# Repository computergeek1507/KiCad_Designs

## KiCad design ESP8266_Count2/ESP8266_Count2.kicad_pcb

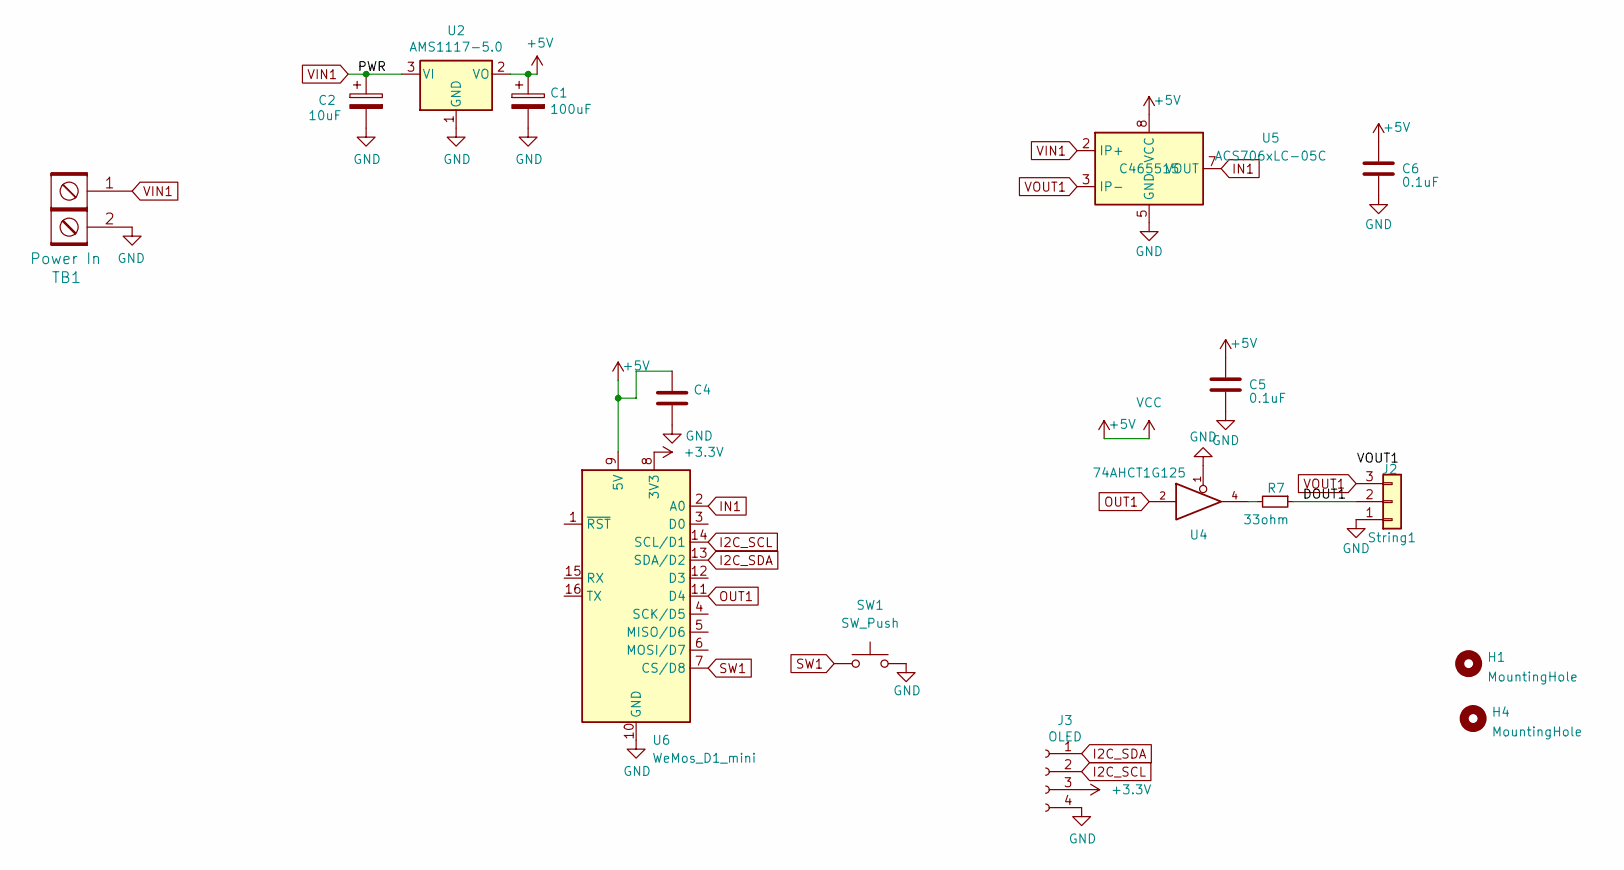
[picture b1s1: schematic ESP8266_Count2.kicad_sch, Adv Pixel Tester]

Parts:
C1: 100uF; C_1206_3216Metric_Pad1.33x1.80mm_HandSolder; LCSC C15008
C2: 10uF; C_0805_2012Metric_Pad1.18x1.45mm_HandSolder; MPN GRM21BR61E106KA73L; Digi-Key_PN 490-5523-1-ND
C4: 0.1uF; C_0603_1608Metric_Pad1.08x0.95mm_HandSolder
C5, C6: 0.1uF; C_0603_1608Metric_Pad1.08x0.95mm_HandSolder; LCSC C14663
H1, H4: MountingHole; MountingHole_2.7mm_M2.5
J2: String1; PhoenixContact_MCV_1,5_3-G-3.81_1x03_P3.81mm_Vertical; MPN 1843619/OSTTJ0311530; Digi-Key_PN 277-5737-ND/ED10555-ND
J3: OLED; OLED-SSD1306-128X64-I2C-THT_2HOLE; MPN PPTC041LFBN-RC; Digi-Key_PN S7002-ND
R7: 33ohm; R_0603_1608Metric_Pad0.98x0.95mm_HandSolder; MPN RC0603JR-0733RL; LCSC_PN C23140
SW1: SW_Push; SW_Push_1P1T_NO_6x6mm_H9.5mm; LCSC C2834918
TB1: Power In; PhoenixContact_MCV_1,5_2-G-3.81_1x02_P3.81mm_Vertical; MPN 4DB-P108-02; Digi-Key_PN A98472-ND
U2: AMS1117-5.0; SOT-223-3_TabPin2; MPN LM1117MPX-50NOPB; LCSC_PN C6187
U4: 74AHCT1G125; TSOP-5_1.65x3.05mm_P0.95mm; MPN 74AHCT1G125W5-7; Digi-Key_PN 74AHCT1G125W5-7DICT-ND
U5: ACS706xLC-05C; SOIC-8_3.9x4.9mm_P1.27mm; LCSC C465515
U6: WeMos_D1_mini; WEMOS_D1_mini_light

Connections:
+3.3V: J3.3, U6.8 (3V3)
+5V: C1.1, C4.1, C5.1, C6.1, U2.2 (VO), U4.5 (VCC), U5.8 (VCC), U6.9 (5V)
/DOUT1: J2.2, R7.1
GND: C1.2, C2.2, C4.2, C5.2, C6.2, J2.1, J3.4, SW1.2, TB1.2, U2.1 (GND), U4.1, U4.3 (GND), U5.5 (GND), U6.10 (GND)
I2C_SCL: J3.2, U6.14 (SCL/D1)
I2C_SDA: J3.1, U6.13 (SDA/D2)
IN1: U5.7 (VOUT), U6.2 (A0)
unnamed: R7.2, U4.4
OUT1: U4.2, U6.11 (D4)
SW1: SW1.1, U6.7 (CS/D8)
VIN1: C2.1, TB1.1, U2.3 (VI), U5.1 (IP+), U5.2 (IP+)
VOUT1: J2.3, U5.3 (IP-), U5.4 (IP-)

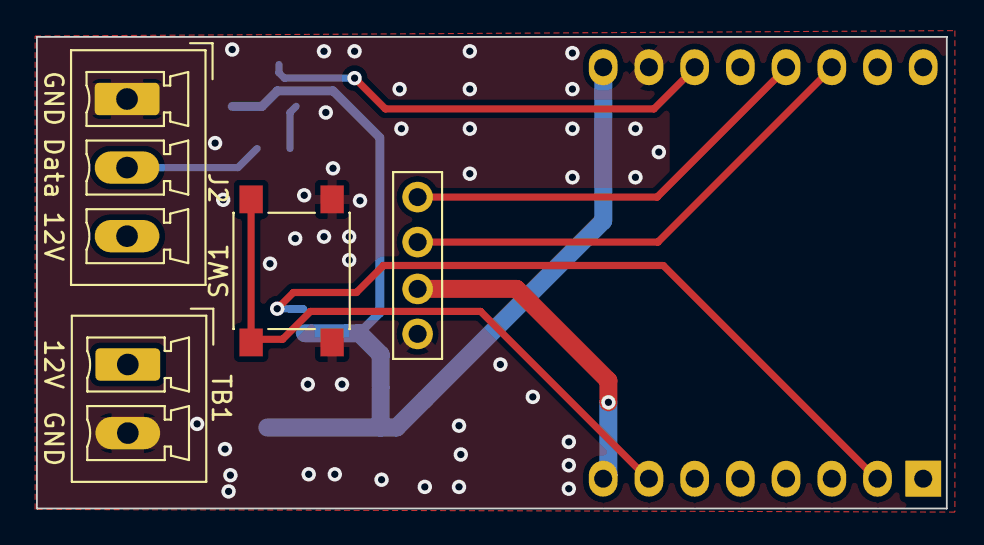
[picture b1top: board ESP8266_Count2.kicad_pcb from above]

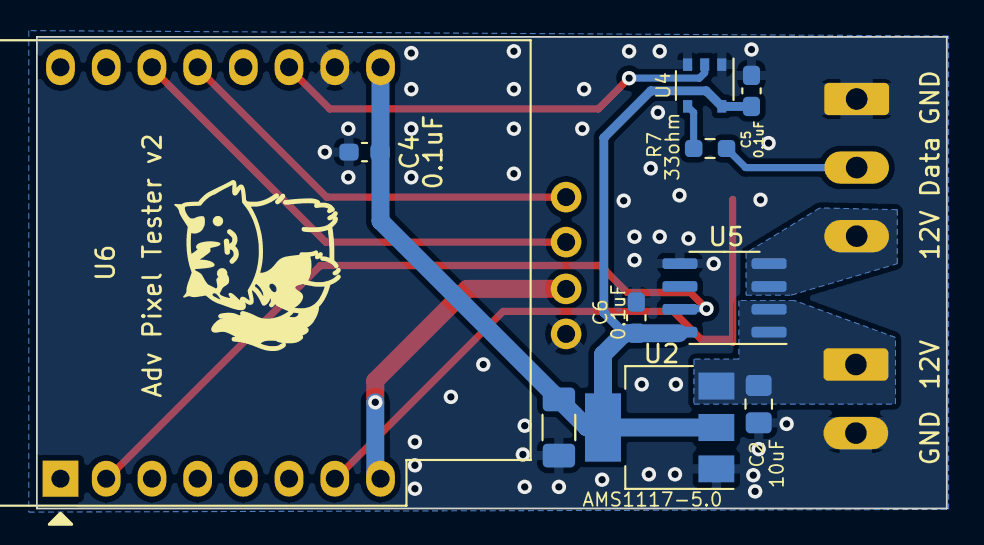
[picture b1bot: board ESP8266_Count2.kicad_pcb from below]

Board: 2 copper layers, 50.5 x 26.2 mm, 16 parts (10 on the bottom side), 12 nets.

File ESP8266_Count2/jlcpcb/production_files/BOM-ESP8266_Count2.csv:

Comment,Designator,Footprint,LCSC
0.1uF,"C4,C5,C6",C_0603_1608Metric_Pad1.08x0.95mm_HandSolder,C14663
100uF,C1,C_1206_3216Metric_Pad1.33x1.80mm_HandSolder,C15008
10uF,C2,C_0805_2012Metric_Pad1.18x1.45mm_HandSolder,C15850
OLED,J3,OLED-SSD1306-128X64-I2C-THT_2HOLE,C225501
33ohm,R7,R_0603_1608Metric_Pad0.98x0.95mm_HandSolder,C23140
SW_Push,SW1,SW_Push_1P1T_NO_6x6mm_H9.5mm,C2834918
ACS706xLC-05C,U5,SOIC-8_3.9x4.9mm_P1.27mm,C465515
AMS1117-5.0,U2,SOT-223-3_TabPin2,C6187
74AHCT1G125,U4,TSOP-5_1.65x3.05mm_P0.95mm,C7484

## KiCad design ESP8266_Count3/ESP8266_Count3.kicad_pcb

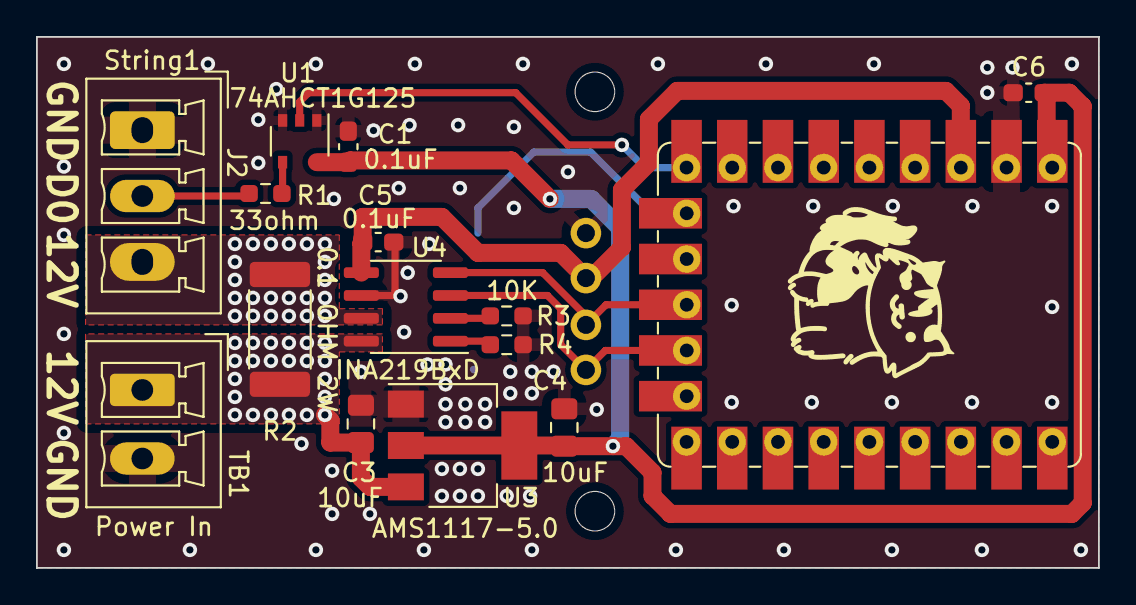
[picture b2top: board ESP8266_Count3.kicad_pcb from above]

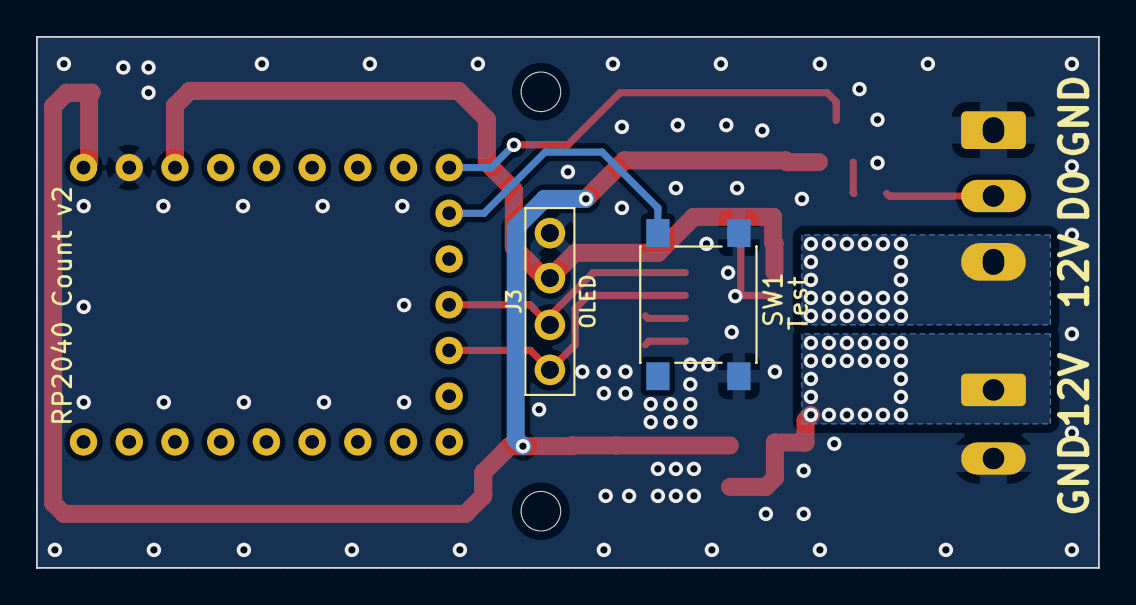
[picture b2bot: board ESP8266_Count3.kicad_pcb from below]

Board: 2 copper layers, 59.0 x 29.5 mm, 17 parts (2 on the bottom side), 13 nets.

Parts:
C1, C5, C6: 0.1uF; C_0603_1608Metric_Pad1.08x0.95mm_HandSolder
C3, C4: 10uF; C_0805_2012Metric_Pad1.18x1.45mm_HandSolder
J2: String1; PhoenixContact_MCV_3.81mm_3.5mm_1x03_Vertical
J3: OLED; OLED-SSD1306-128X64-I2C-THT_2HOLE
R1: 33ohm; R_0603_1608Metric_Pad0.98x0.95mm_HandSolder
R2: 0.1 OHM 2W; R_2512_6332Metric_Pad1.40x3.35mm_HandSolder
R3, R4: 10K; R_0603_1608Metric_Pad0.98x0.95mm_HandSolder
SW1: Test; SW_Push_1P1T_NO_6x6mm_H9.5mm
TB1: Power In; PhoenixContact_MCV_1,5_2-G-3.81_1x02_P3.81mm_Vertical
U1: 74AHCT1G125; TSOP-5_1.65x3.05mm_P0.95mm
U3: AMS1117-5.0; SOT-223-3_TabPin2
U4: INA219BxD; SOIC-8_3.9x4.9mm_P1.27mm
U5: RP2040-Tiny; RP2040-Tiny_Scott

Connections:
+3.3V: C5.1, J3.3, U4.5 (VS), U5.3 (3V3)
+5V: C1.1, C4.1, C6.2, U1.5 (VCC), U3.2 (VO), U5.1 (5V)
/DOUT1: J2.2, R1.1
GND: C1.2, C3.2, C4.2, C5.2, C6.1, J2.1, J3.4, R3.2, R4.2, SW1.2, TB1.2, U1.1, U1.3 (GND), U3.1 (GND), U4.6 (GND), U5.2 (GND)
I2C_SCL: J3.2, U4.4 (SCL), U5.12 (GPIO11)
I2C_SDA: J3.1, U4.3 (SDA), U5.13 (GPIO10)
unnamed: R1.2, U1.4
unnamed: R3.1, U4.2 (A0)
unnamed: R4.1, U4.1 (A1)
OUT1: U1.2, U5.9 (GPIO14)
SW1: SW1.1, U5.10 (GPIO13)
VIN1: C3.1, R2.1, TB1.1, U3.3 (VI), U4.8 (IN+)
VOUT1: J2.3, R2.2, U4.7 (IN-)

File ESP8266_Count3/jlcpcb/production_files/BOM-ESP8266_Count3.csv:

Comment,Designator,Footprint,LCSC
0.1uF,"C1,C2,C5",C_0603_1608Metric_Pad1.08x0.95mm_HandSolder,C14663
10uF,"C3,C4",C_0805_2012Metric_Pad1.18x1.45mm_HandSolder,C15850
OLED,J3,OLED-SSD1306-128X64-I2C-THT_2HOLE,C225501
33ohm,R1,R_0603_1608Metric_Pad0.98x0.95mm_HandSolder,C23140
10K,"R3,R4",R_0603_1608Metric_Pad0.98x0.95mm_HandSolder,C25804
Test,SW1,SW_Push_1P1T_NO_6x6mm_H9.5mm,C2834918
0.1 OHM 2W,R2,R_2512_6332Metric_Pad1.40x3.35mm_HandSolder,C2903476
AMS1117-5.0,U3,SOT-223-3_TabPin2,C6187
74AHCT1G125,U1,TSOP-5_1.65x3.05mm_P0.95mm,C7484
INA219BxD,U4,SOIC-8_3.9x4.9mm_P1.27mm,C87469

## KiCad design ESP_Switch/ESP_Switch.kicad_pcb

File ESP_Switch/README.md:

# Copyright and Disclaimer
Copyright: Scott Hanson

This documentation describes Open Hardware and is licensed under the CERN OHL v. 1.2.

You may redistribute and modify this documentation under the terms of the CERN OHL v.1.2. (http://ohwr.org/cernohl). This documentation is distributed WITHOUT ANY EXPRESS OR IMPLIED WARRANTY, INCLUDING OF MERCHANTABILITY, SATISFACTORY QUALITY AND FITNESS FOR A PARTICULAR PURPOSE. Please see the CERN OHL v.1.2 for applicable conditions

# ESP-12E Breakout Board

ESP-12E ESP8266 Wifi Module Breakout Board. The design was made with all through hole components for easy assembly by most users. Open source applications were used to create this controller. [KiCad](http://kicad-pcb.org/) was used for the PCB design, and [LibreOffice](https://www.libreoffice.org/) for the documentation.

To order your own PCB upload the gerber.zip file to your favorite PCB manufacture of choice, I personally use [jlcpcb.com](https://jlcpcb.com/).

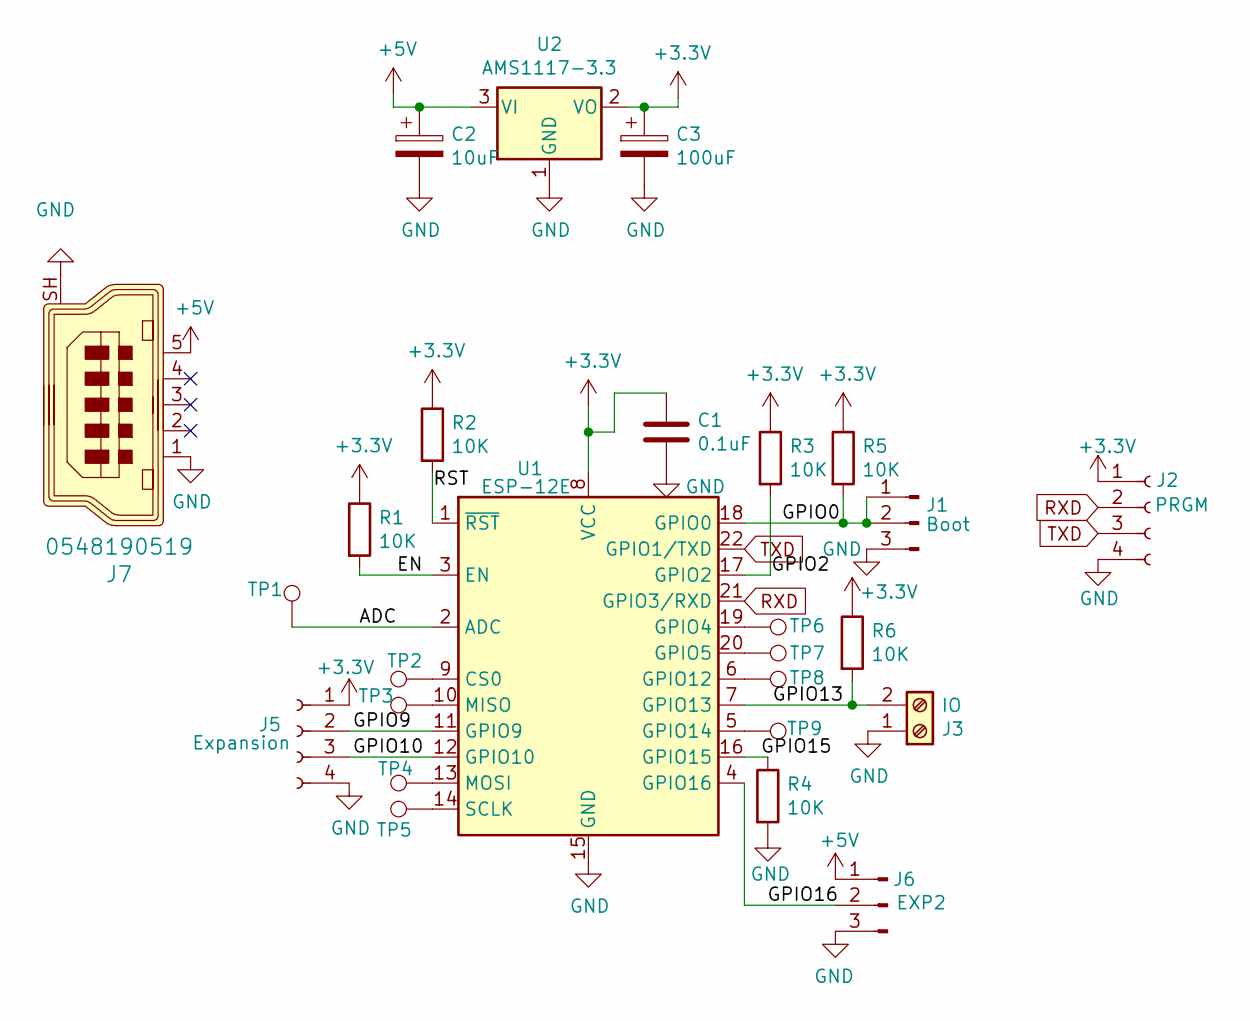
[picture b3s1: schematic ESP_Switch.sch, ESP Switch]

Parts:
C1: 0.1uF; C_0805_2012Metric_Pad1.15x1.40mm_HandSolder
C2: 10uF; C_0805_2012Metric_Pad1.15x1.40mm_HandSolder
C3: 100uF; C_1206_3216Metric_Pad1.42x1.75mm_HandSolder
J1: Boot; PinHeader_1x03_P2.54mm_Vertical
J2: PRGM; PinHeader_1x04_P2.54mm_Vertical
J3: IO; TerminalBlock_Phoenix_MKDS-1,5-2_1x02_P5.00mm_Horizontal
J5: Expansion; PinHeader_1x04_P2.54mm_Vertical
J6: EXP2; PinHeader_1x03_P2.54mm_Vertical
J7: 0548190519; USB_Mini_B_Female_548190519; MPN 0548190519; Digi-Key_PN WM17115-ND
R1, R2, R3, R4, R5, R6: 10K; R_0805_2012Metric_Pad1.15x1.40mm_HandSolder
TP1, TP2, TP3, TP4, TP5, TP6, TP7, TP8, TP9: ESP_SwitchPoint; ESP_SwitchPoint_Pad_1.0x1.0mm
U1: ESP-12E
U2: AMS1117-3.3; SOT-223-3_TabPin2

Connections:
+3V3: C1.1, C3.1, J2.1, J5.1, R1.1, R2.1, R3.1, R5.1, R6.1, U1.8 (VCC), U2.2 (VO)
+5V: C2.1, J6.1, J7.5, U2.3 (VI)
/ADC: TP1.1, U1.2 (ADC)
/EN: R1.2, U1.3 (EN)
/GPIO0: J1.1, J1.2, R5.2, U1.18 (GPIO0)
/GPIO2: R3.2, U1.17 (GPIO2)
/GPIO9: J5.2, U1.11 (GPIO9)
/GPIO10: J5.3, U1.12 (GPIO10)
/GPIO13: J3.2, R6.2, U1.7 (GPIO13)
/GPIO15: R4.1, U1.16 (GPIO15)
/GPIO16: J6.2, U1.4 (GPIO16)
/RST: R2.2, U1.1 (~RST)
GND: C1.2, C2.2, C3.2, J1.3, J2.4, J3.1, J5.4, J6.3, J7.1, J7.SH, R4.2, U1.15 (GND), U2.1 (GND)
unnamed: TP2.1, U1.9 (CS0)
unnamed: TP3.1, U1.10 (MISO)
unnamed: TP4.1, U1.13 (MOSI)
unnamed: TP5.1, U1.14 (SCLK)
unnamed: TP6.1, U1.19 (GPIO4)
unnamed: TP7.1, U1.20 (GPIO5)
unnamed: TP8.1, U1.6 (GPIO12)
unnamed: TP9.1, U1.5 (GPIO14)
RXD: J2.2, U1.21 (GPIO3/RXD)
TXD: J2.3, U1.22 (GPIO1/TXD)

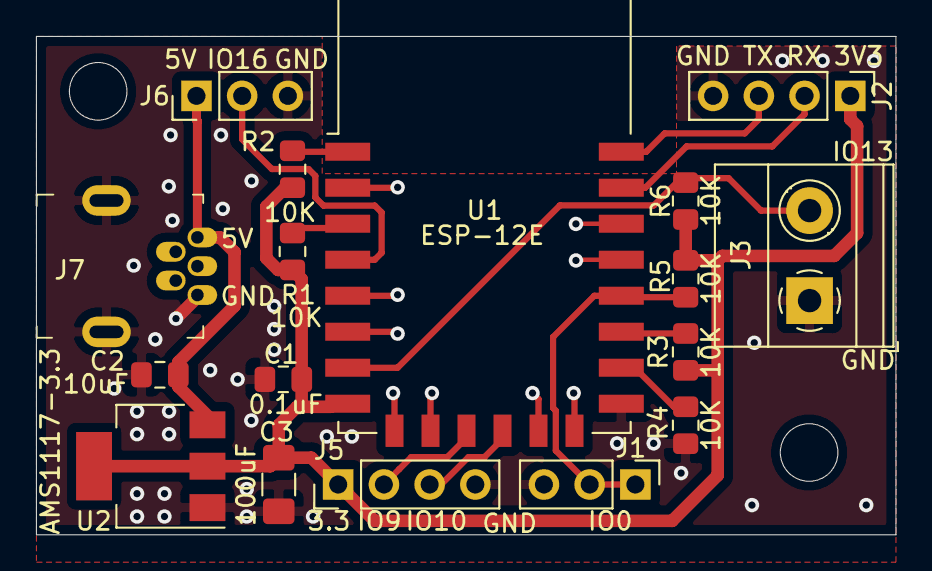
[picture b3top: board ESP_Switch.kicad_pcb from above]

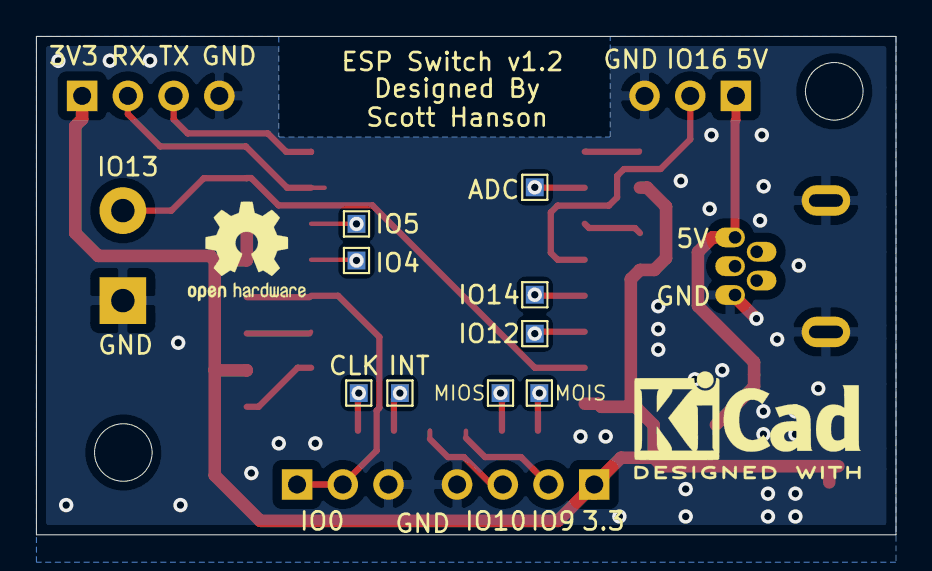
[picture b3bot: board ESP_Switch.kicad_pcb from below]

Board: 2 copper layers, 47.8 x 27.7 mm, 26 parts (9 on the bottom side), 23 nets.

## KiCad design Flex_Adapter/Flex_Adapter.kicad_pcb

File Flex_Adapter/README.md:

# Copyright and Disclaimer
Copyright: Scott Hanson

This documentation describes Open Hardware and is licensed under the CERN OHL v. 1.2.

You may redistribute and modify this documentation under the terms of the CERN OHL v.1.2. (http://ohwr.org/cernohl). This documentation is distributed WITHOUT ANY EXPRESS OR IMPLIED WARRANTY, INCLUDING OF MERCHANTABILITY, SATISFACTORY QUALITY AND FITNESS FOR A PARTICULAR PURPOSE. Please see the CERN OHL v.1.2 for applicable conditions

# Flex Adapter

Adapter to use HolidayCoro Flex Expansion board with the PB16 and Kulp Controllers. The design was made with all through hole components for easy assembly by most users. Open source applications were used to create this controller. [KiCad](http://kicad-pcb.org/) was used for the PCB design, and [LibreOffice](https://www.libreoffice.org/) for the documentation.

To order your own PCB upload the gerber.zip file to your favorite PCB manufacture of choice, I personally use [jlcpcb.com](https://jlcpcb.com/).

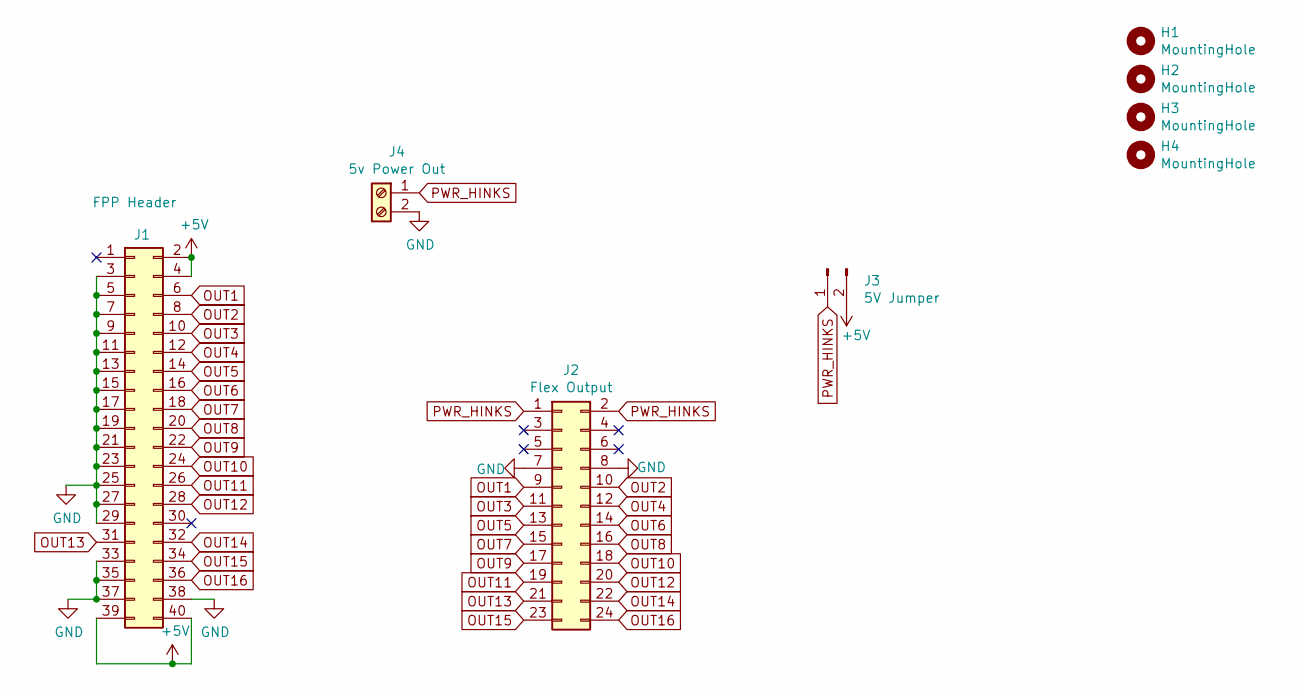
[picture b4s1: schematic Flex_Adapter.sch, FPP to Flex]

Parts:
H1, H2, H3, H4: MountingHole; MountingHole_4.3mm_M4
J1: FPP Header; IDC-Header_2x20_P2.54mm_Vertical; MPN SBH11-PBPC-D20-ST-BK; Digi-Key_PN S9175-ND
J2: Flex Output; OST_302-S241; MPN 302-S241; Digi-Key_PN ED10525-ND
J3: 5V Jumper; PinHeader_1x02_P2.54mm_Vertical
J4: 5v Power Out; PHOENIX_MKDS1_2-3.81; MPN 1727010; Digi-Key_PN 277-1947-ND

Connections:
+5V: J1.2, J1.4, J1.39, J1.40, J3.2
GND: J1.3, J1.5, J1.7, J1.9, J1.11, J1.13, J1.15, J1.17, J1.19, J1.21, J1.23, J1.25, J1.27, J1.29, J1.33, J1.35, J1.37, J1.38, J2.7, J2.8, J4.2
OUT1: J1.6, J2.9
OUT2: J1.8, J2.10
OUT3: J1.10, J2.11
OUT4: J1.12, J2.12
OUT5: J1.14, J2.13
OUT6: J1.16, J2.14
OUT7: J1.18, J2.15
OUT8: J1.20, J2.16
OUT9: J1.22, J2.17
OUT10: J1.24, J2.18
OUT11: J1.26, J2.19
OUT12: J1.28, J2.20
OUT13: J1.31, J2.21
OUT14: J1.32, J2.22
OUT15: J1.34, J2.23
OUT16: J1.36, J2.24
PWR_HINKS: J2.1, J2.2, J3.1, J4.1

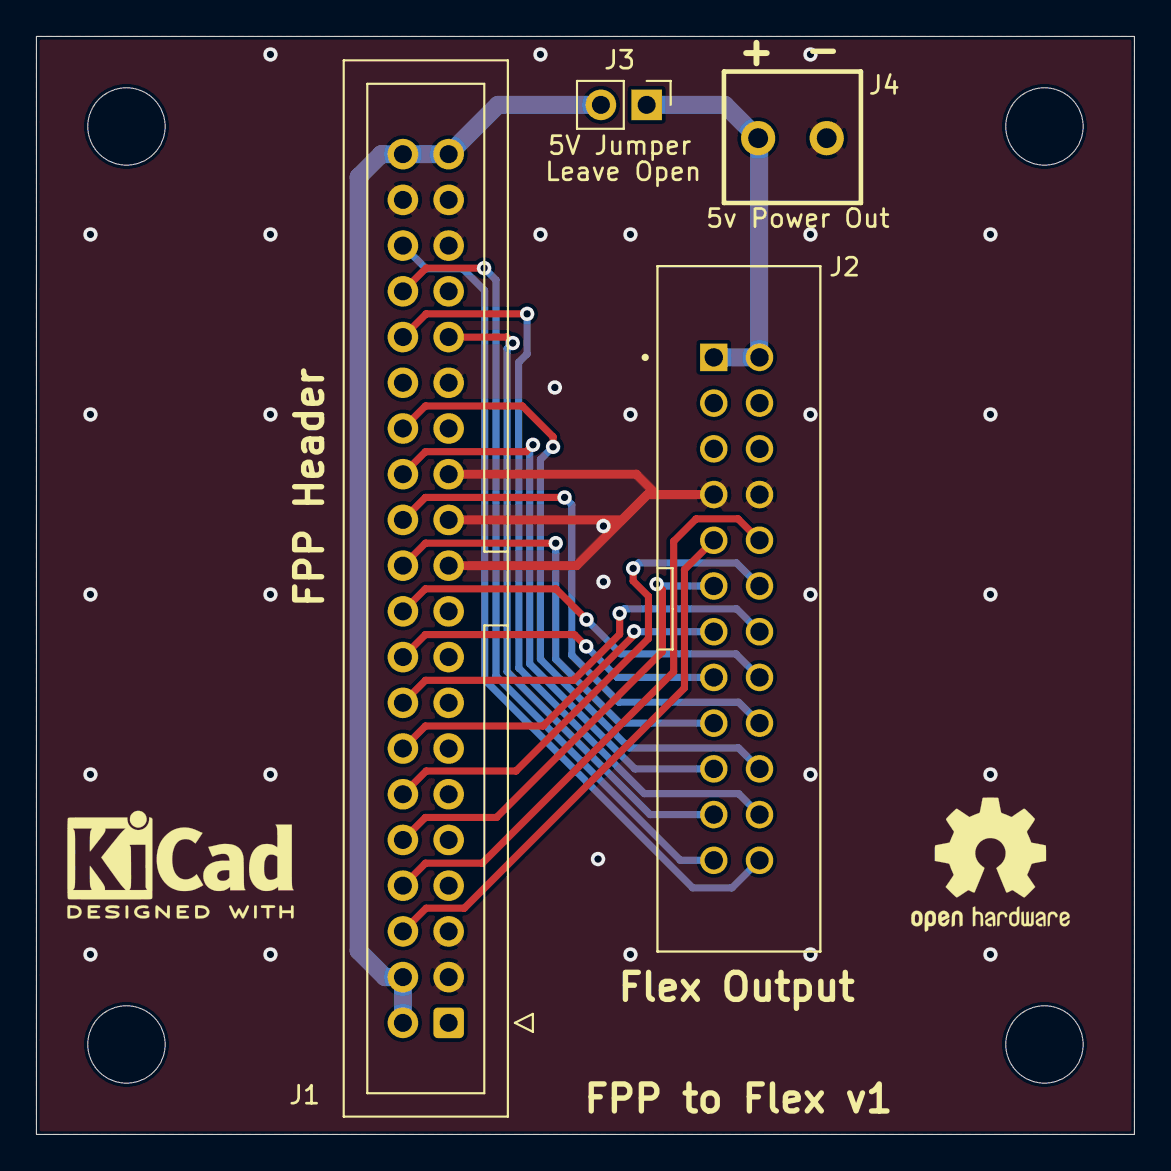
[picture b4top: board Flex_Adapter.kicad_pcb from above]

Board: 2 copper layers, 61.0 x 61.0 mm, 8 parts (0 on the bottom side), 19 nets.

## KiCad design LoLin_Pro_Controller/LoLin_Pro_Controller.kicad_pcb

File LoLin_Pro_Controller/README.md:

# Copyright and Disclaimer
Copyright: Scott Hanson

This documentation describes Open Hardware and is licensed under the CERN OHL v. 1.2.

You may redistribute and modify this documentation under the terms of the CERN OHL v.1.2. (http://ohwr.org/cernohl). This documentation is distributed WITHOUT ANY EXPRESS OR IMPLIED WARRANTY, INCLUDING OF MERCHANTABILITY, SATISFACTORY QUALITY AND FITNESS FOR A PARTICULAR PURPOSE. Please see the CERN OHL v.1.2 for applicable conditions

# LoLin Pro Controller

6 port Controller breakout for LoLin Pro ESP32. The design was made with all through hole components for easy assembly by most users. Open source applications were used to create this controller. [KiCad](http://kicad-pcb.org/) was used for the PCB design, and [LibreOffice](https://www.libreoffice.org/) for the documentation.

To order your own PCB upload the gerber.zip file to your favorite PCB manufacture of choice, I personally use [jlcpcb.com](https://jlcpcb.com/).

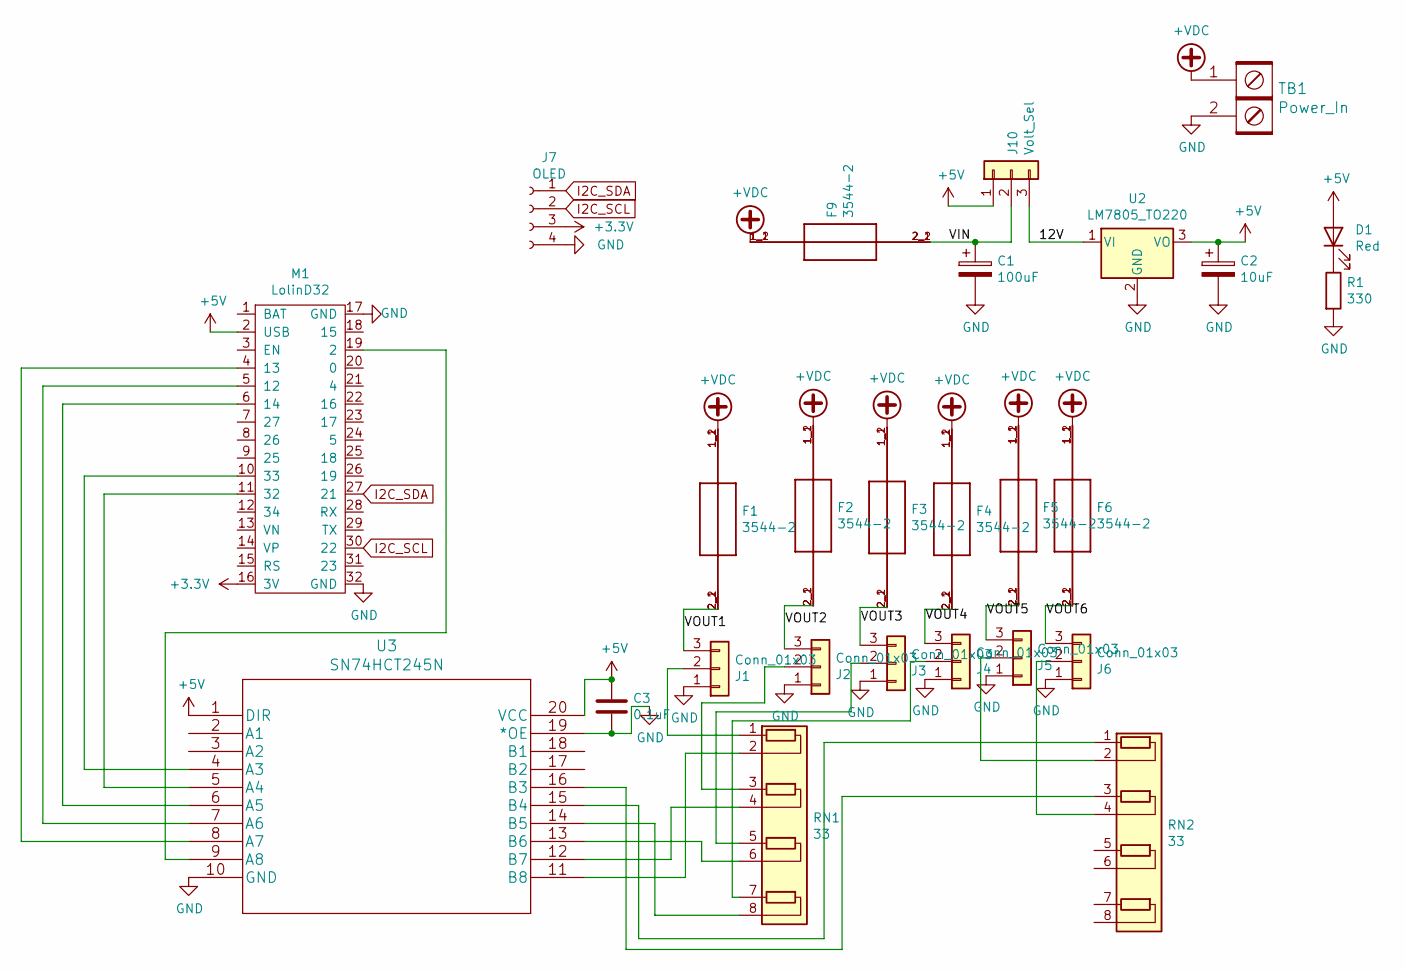
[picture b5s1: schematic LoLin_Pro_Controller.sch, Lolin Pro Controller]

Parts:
C1: 100uF; CP_Radial_D8.0mm_P3.50mm
C2: 10uF; CP_Radial_D5.0mm_P2.00mm
C3: 0.1uF; C_Rect_L7.0mm_W2.0mm_P5.00mm
D1: Red; LED_D3.0mm
F1, F2, F3, F4, F5, F6, F9: 3544-2; FUSE_3544-2
J1, J2, J3, J4, J5, J6: Conn_01x03; PhoenixContact_MCV_1,5_3-G-3.5_1x03_P3.50mm_Vertical
J7: OLED; OLED-SSD1306-128X64-I2C-THT
J10: Volt_Sel; PinHeader_1x03_P2.54mm_Vertical
M1: LolinD32
R1: 330; R_Axial_DIN0207_L6.3mm_D2.5mm_P7.62mm_Horizontal
RN1, RN2: 33; R_Array_SIP8
TB1: Power_In; BARRIER_BLOCK_1ROW_2POS_P8.26MM
U2: LM7805_TO220; TO-220-3_Horizontal_TabDown
U3: SN74HCT245N

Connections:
+3V3: J7.3, M1.16 (3V)
+5V: C2.1, C3.1, D1.2 (A), J10.1, M1.2 (USB), U2.3 (VO), U3.1 (DIR), U3.20 (VCC)
+VDC: F1.1_1 (1), F1.1_2 (1), F2.1_1 (1), F2.1_2 (1), F3.1_1 (1), F3.1_2 (1), F4.1_1 (1), F4.1_2 (1), F5.1_1 (1), F5.1_2 (1), F6.1_1 (1), F6.1_2 (1), F9.1_1 (1), F9.1_2 (1), TB1.1
/12V: J10.3, U2.1 (VI)
/VIN: C1.1, F9.2_1 (2), F9.2_2 (2), J10.2
/VOUT1: F1.2_1 (2), F1.2_2 (2), J1.3
/VOUT2: F2.2_1 (2), F2.2_2 (2), J2.3
/VOUT3: F3.2_1 (2), F3.2_2 (2), J3.3
/VOUT4: F4.2_1 (2), F4.2_2 (2), J4.3
/VOUT5: F5.2_1 (2), F5.2_2 (2), J5.3
/VOUT6: F6.2_1 (2), F6.2_2 (2), J6.3
GND: C1.2, C2.2, C3.2, J1.1, J2.1, J3.1, J4.1, J5.1, J6.1, J7.4, M1.17 (GND), M1.32 (GND), R1.2, TB1.2, U2.2 (GND), U3.10 (GND), U3.19 (*OE)
I2C_SCL: J7.2, M1.30 (22)
I2C_SDA: J7.1, M1.27 (21)
unnamed: D1.1 (K), R1.1
unnamed: J1.2, RN1.1 (R1.1)
unnamed: J2.2, RN1.3 (R2.1)
unnamed: J3.2, RN1.5 (R3.1)
unnamed: J4.2, RN1.7 (R4.1)
unnamed: J5.2, RN2.2 (R1.2)
unnamed: J6.2, RN2.4 (R2.2)
unnamed: M1.4 (13), U3.8 (A7)
unnamed: M1.5 (12), U3.7 (A6)
unnamed: M1.6 (14), U3.6 (A5)
unnamed: M1.10 (33), U3.4 (A3)
unnamed: M1.11 (32), U3.5 (A4)
unnamed: M1.19 (2), U3.9 (A8)
unnamed: RN1.2 (R1.2), U3.11 (B8)
unnamed: RN1.4 (R2.2), U3.12 (B7)
unnamed: RN1.6 (R3.2), U3.13 (B6)
unnamed: RN1.8 (R4.2), U3.14 (B5)
unnamed: RN2.1 (R1.1), U3.15 (B4)
unnamed: RN2.3 (R2.1), U3.16 (B3)

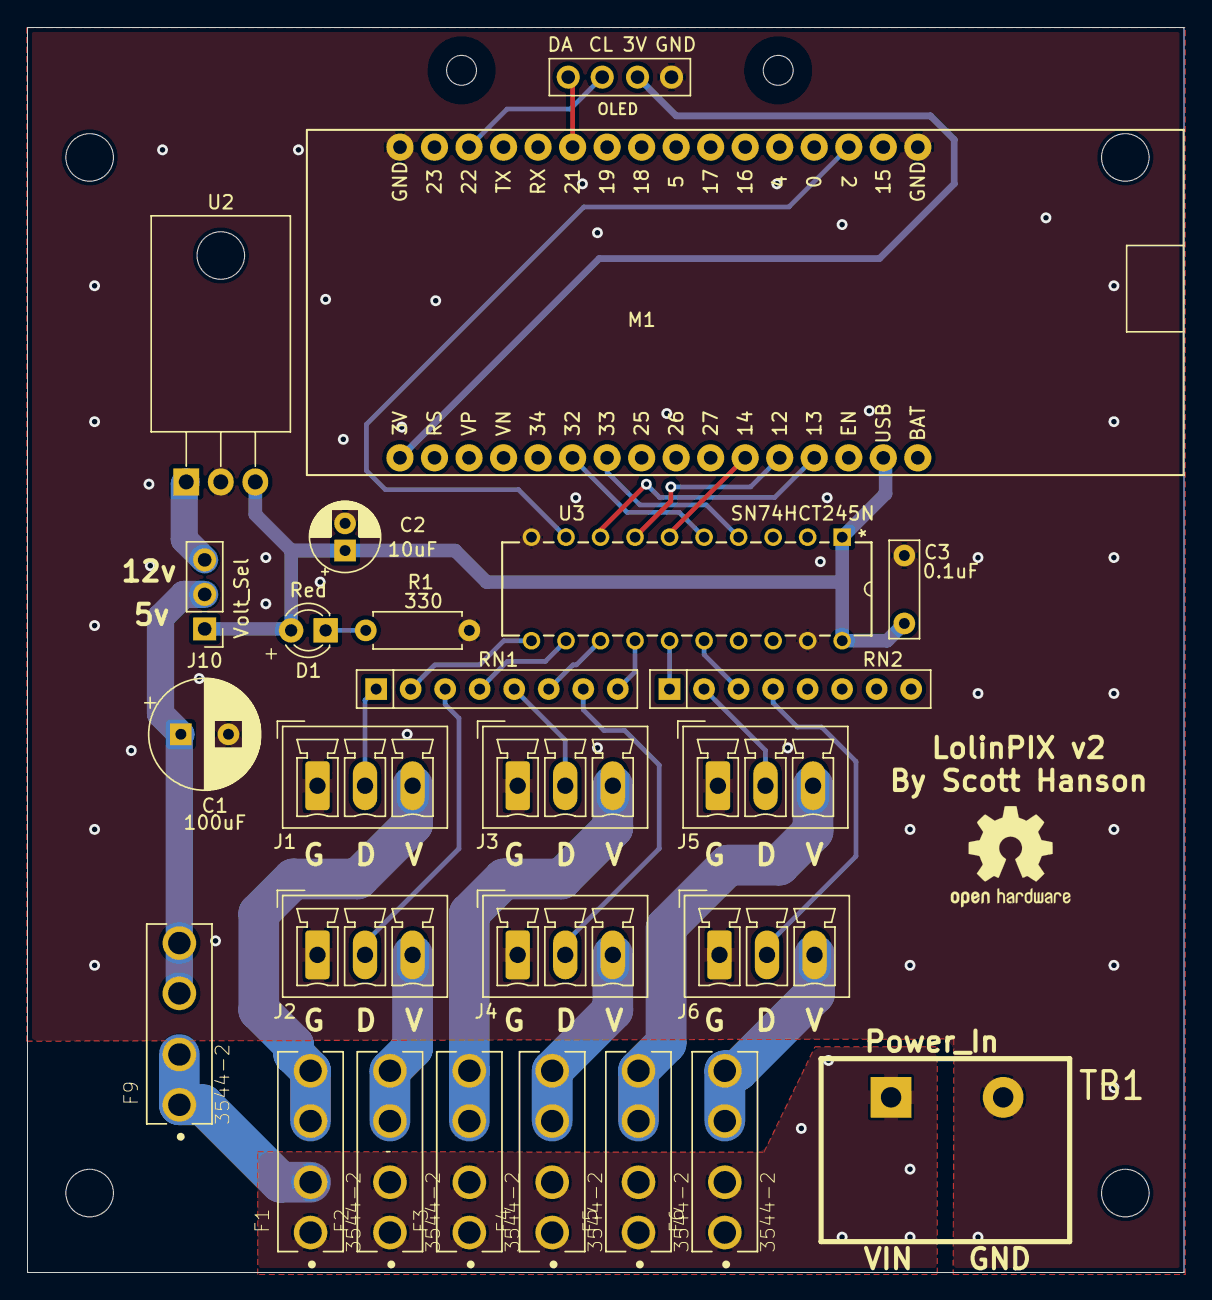
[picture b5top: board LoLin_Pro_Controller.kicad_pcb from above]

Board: 2 copper layers, 85.1 x 91.6 mm, 30 parts (0 on the bottom side), 33 nets.

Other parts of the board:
H1, H2, H3, H4: MountingHole_3.5mm

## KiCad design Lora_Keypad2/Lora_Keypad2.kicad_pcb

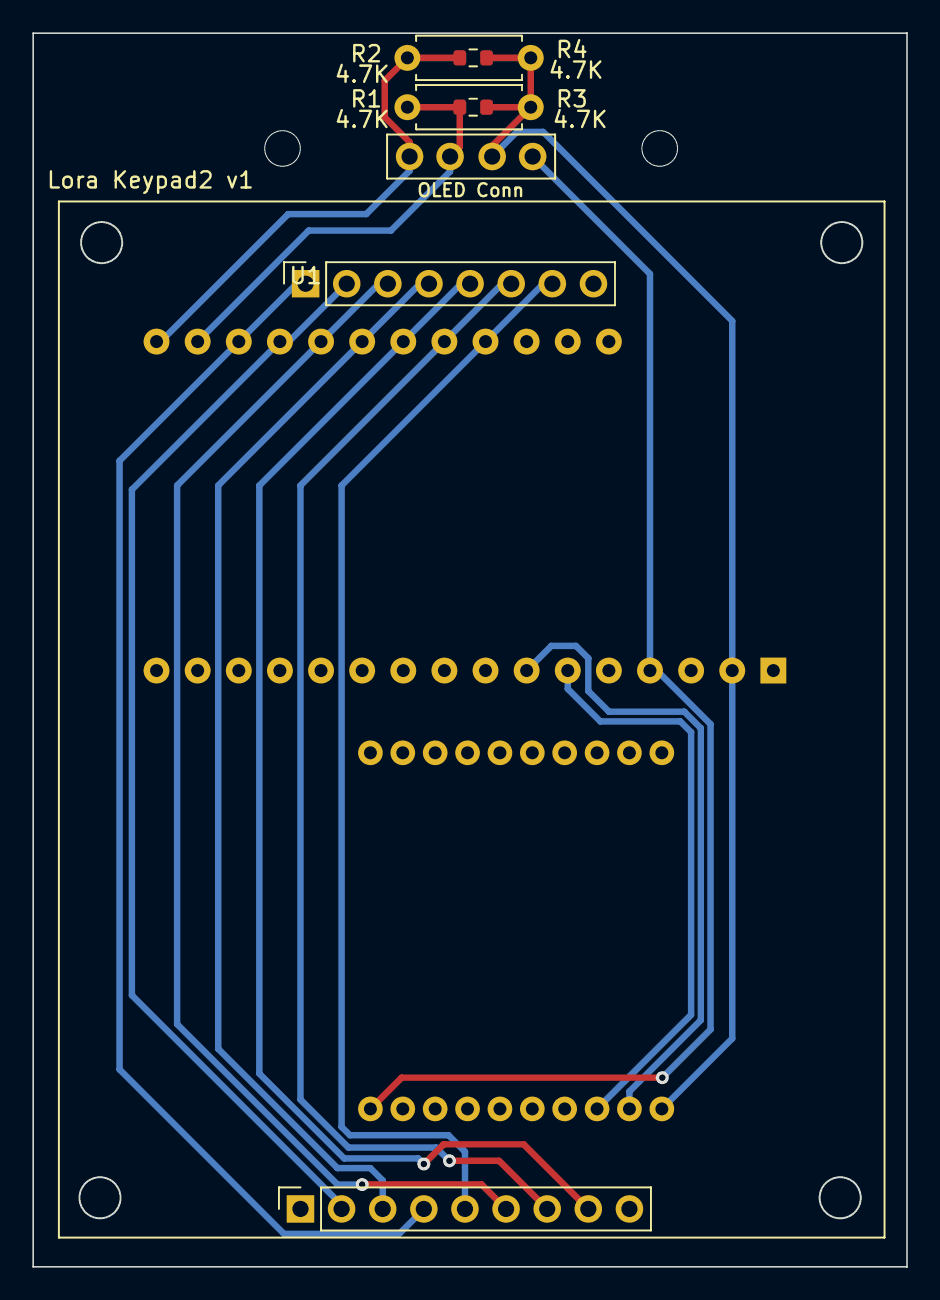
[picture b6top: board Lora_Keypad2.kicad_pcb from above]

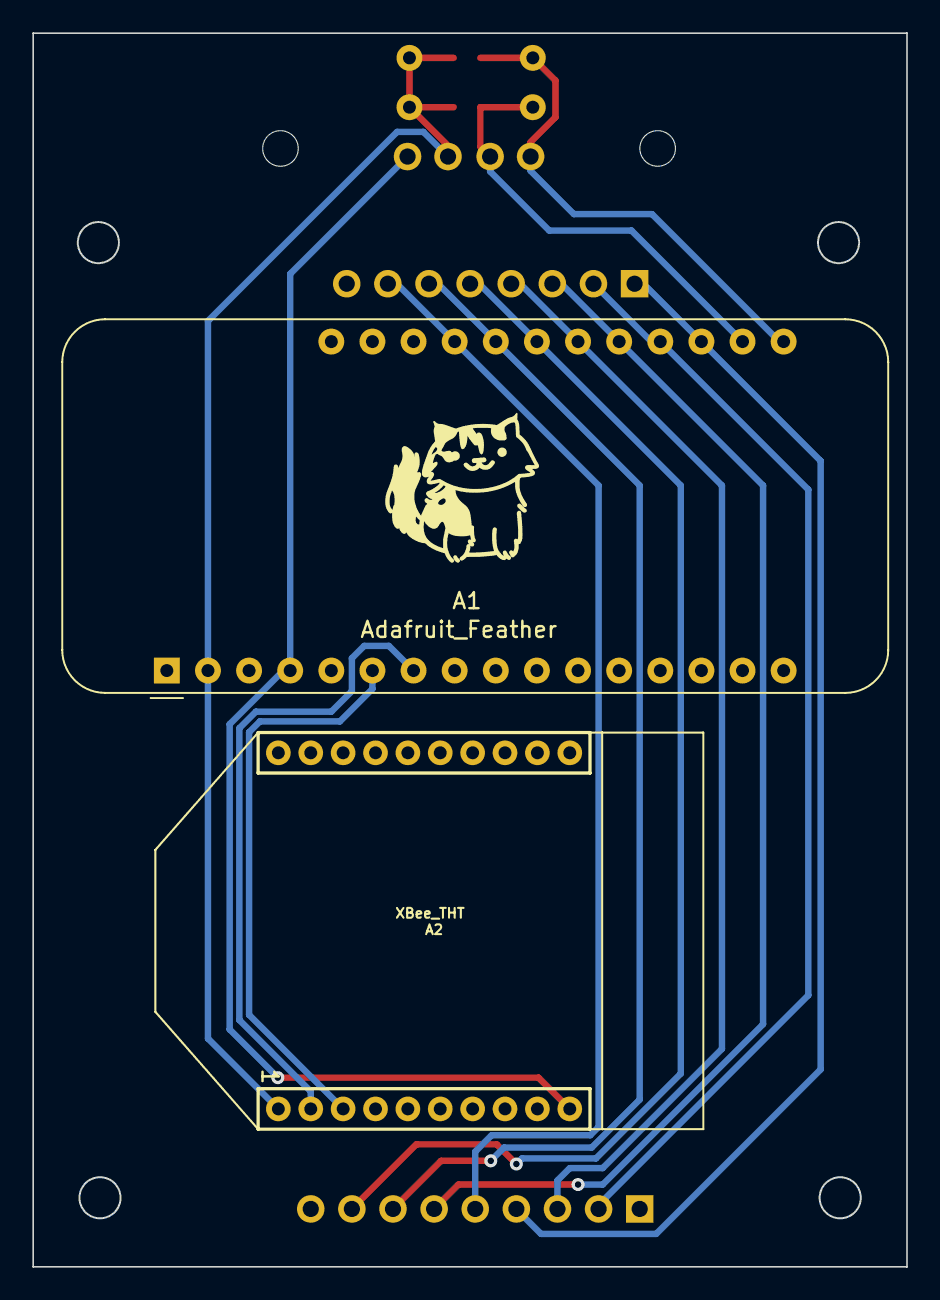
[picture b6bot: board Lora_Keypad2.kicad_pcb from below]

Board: 2 copper layers, 54.0 x 76.2 mm, 8 parts (2 on the bottom side), 13 nets.

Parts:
A1: Adafruit_Feather
A2: XBee_THT; XBEE
J1: OLED Conn; OLED-SSD1306-128X64-I2C-THT_2HOLE
R1, R2: 4.7K; R_0603_1608Metric
R3, R4: 4.7K; R_Axial_DIN0207_L6.3mm_D2.5mm_P7.62mm_Horizontal
U1: 3x4_keypad

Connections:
+3.3V: A1.2 (3V3), A2.1 (VCC), J1.3, R1.1, R2.1, R3.1, R4.1
C1: A1.19 (D0), U1.A1 (C1), U1.B4 (C1)
C2: A1.20 (D1), U1.A2 (C2), U1.B2 (C2)
C3: A1.21 (D2), U1.A3 (C3), U1.B6 (C3)
GND: A1.4 (GND), A2.10 (GND), J1.4
I2C_SCL: A1.18 (SCL), J1.2, R1.2, R3.2
I2C_SDA: A1.17 (SDA), J1.1, R2.2, R4.2
R1: A1.22 (D3), U1.A4 (R1), U1.B3 (R1)
R2: A1.23 (D4), U1.A5 (R2), U1.B8 (R2)
R3: A1.24 (D5), U1.A6 (R3), U1.B7 (R3)
R4: A1.25 (D6), U1.A7 (R4), U1.B5 (R4)
RX: A1.7 (A2), A2.2 (DOUT/DIO13)
TX: A1.6 (A1), A2.3 (DIN/~CONFIG/DIO14)

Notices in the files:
parts and their libraries:
Copyright 2016 Accelerated Designs. All rights reserved.
